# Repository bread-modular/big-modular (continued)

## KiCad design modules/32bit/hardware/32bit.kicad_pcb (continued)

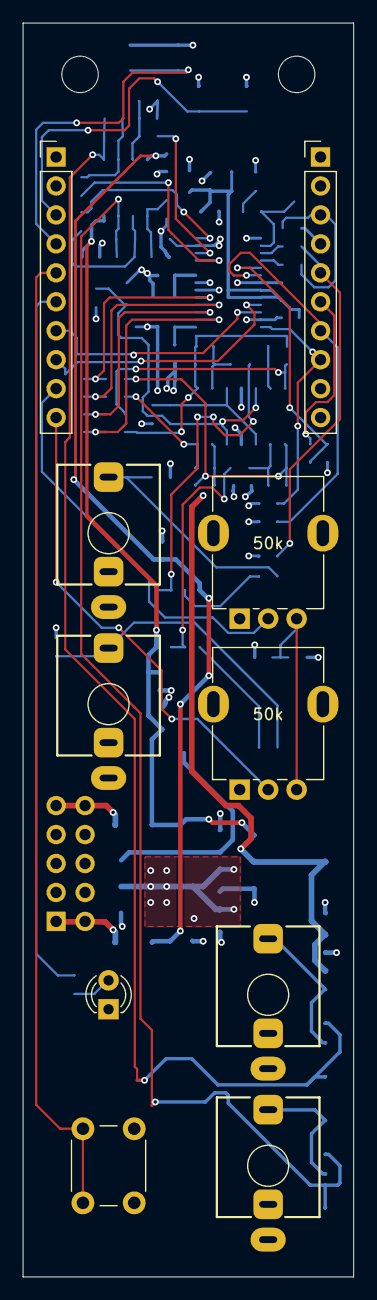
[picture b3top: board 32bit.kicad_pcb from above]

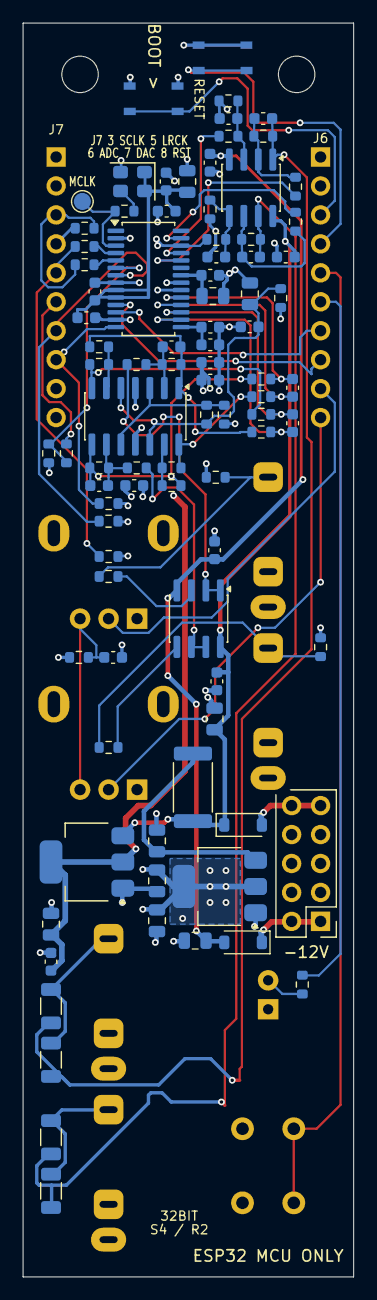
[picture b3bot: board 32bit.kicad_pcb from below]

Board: 4 copper layers, 29.0 x 110.0 mm, 100 parts (90 on the bottom side), 63 nets.

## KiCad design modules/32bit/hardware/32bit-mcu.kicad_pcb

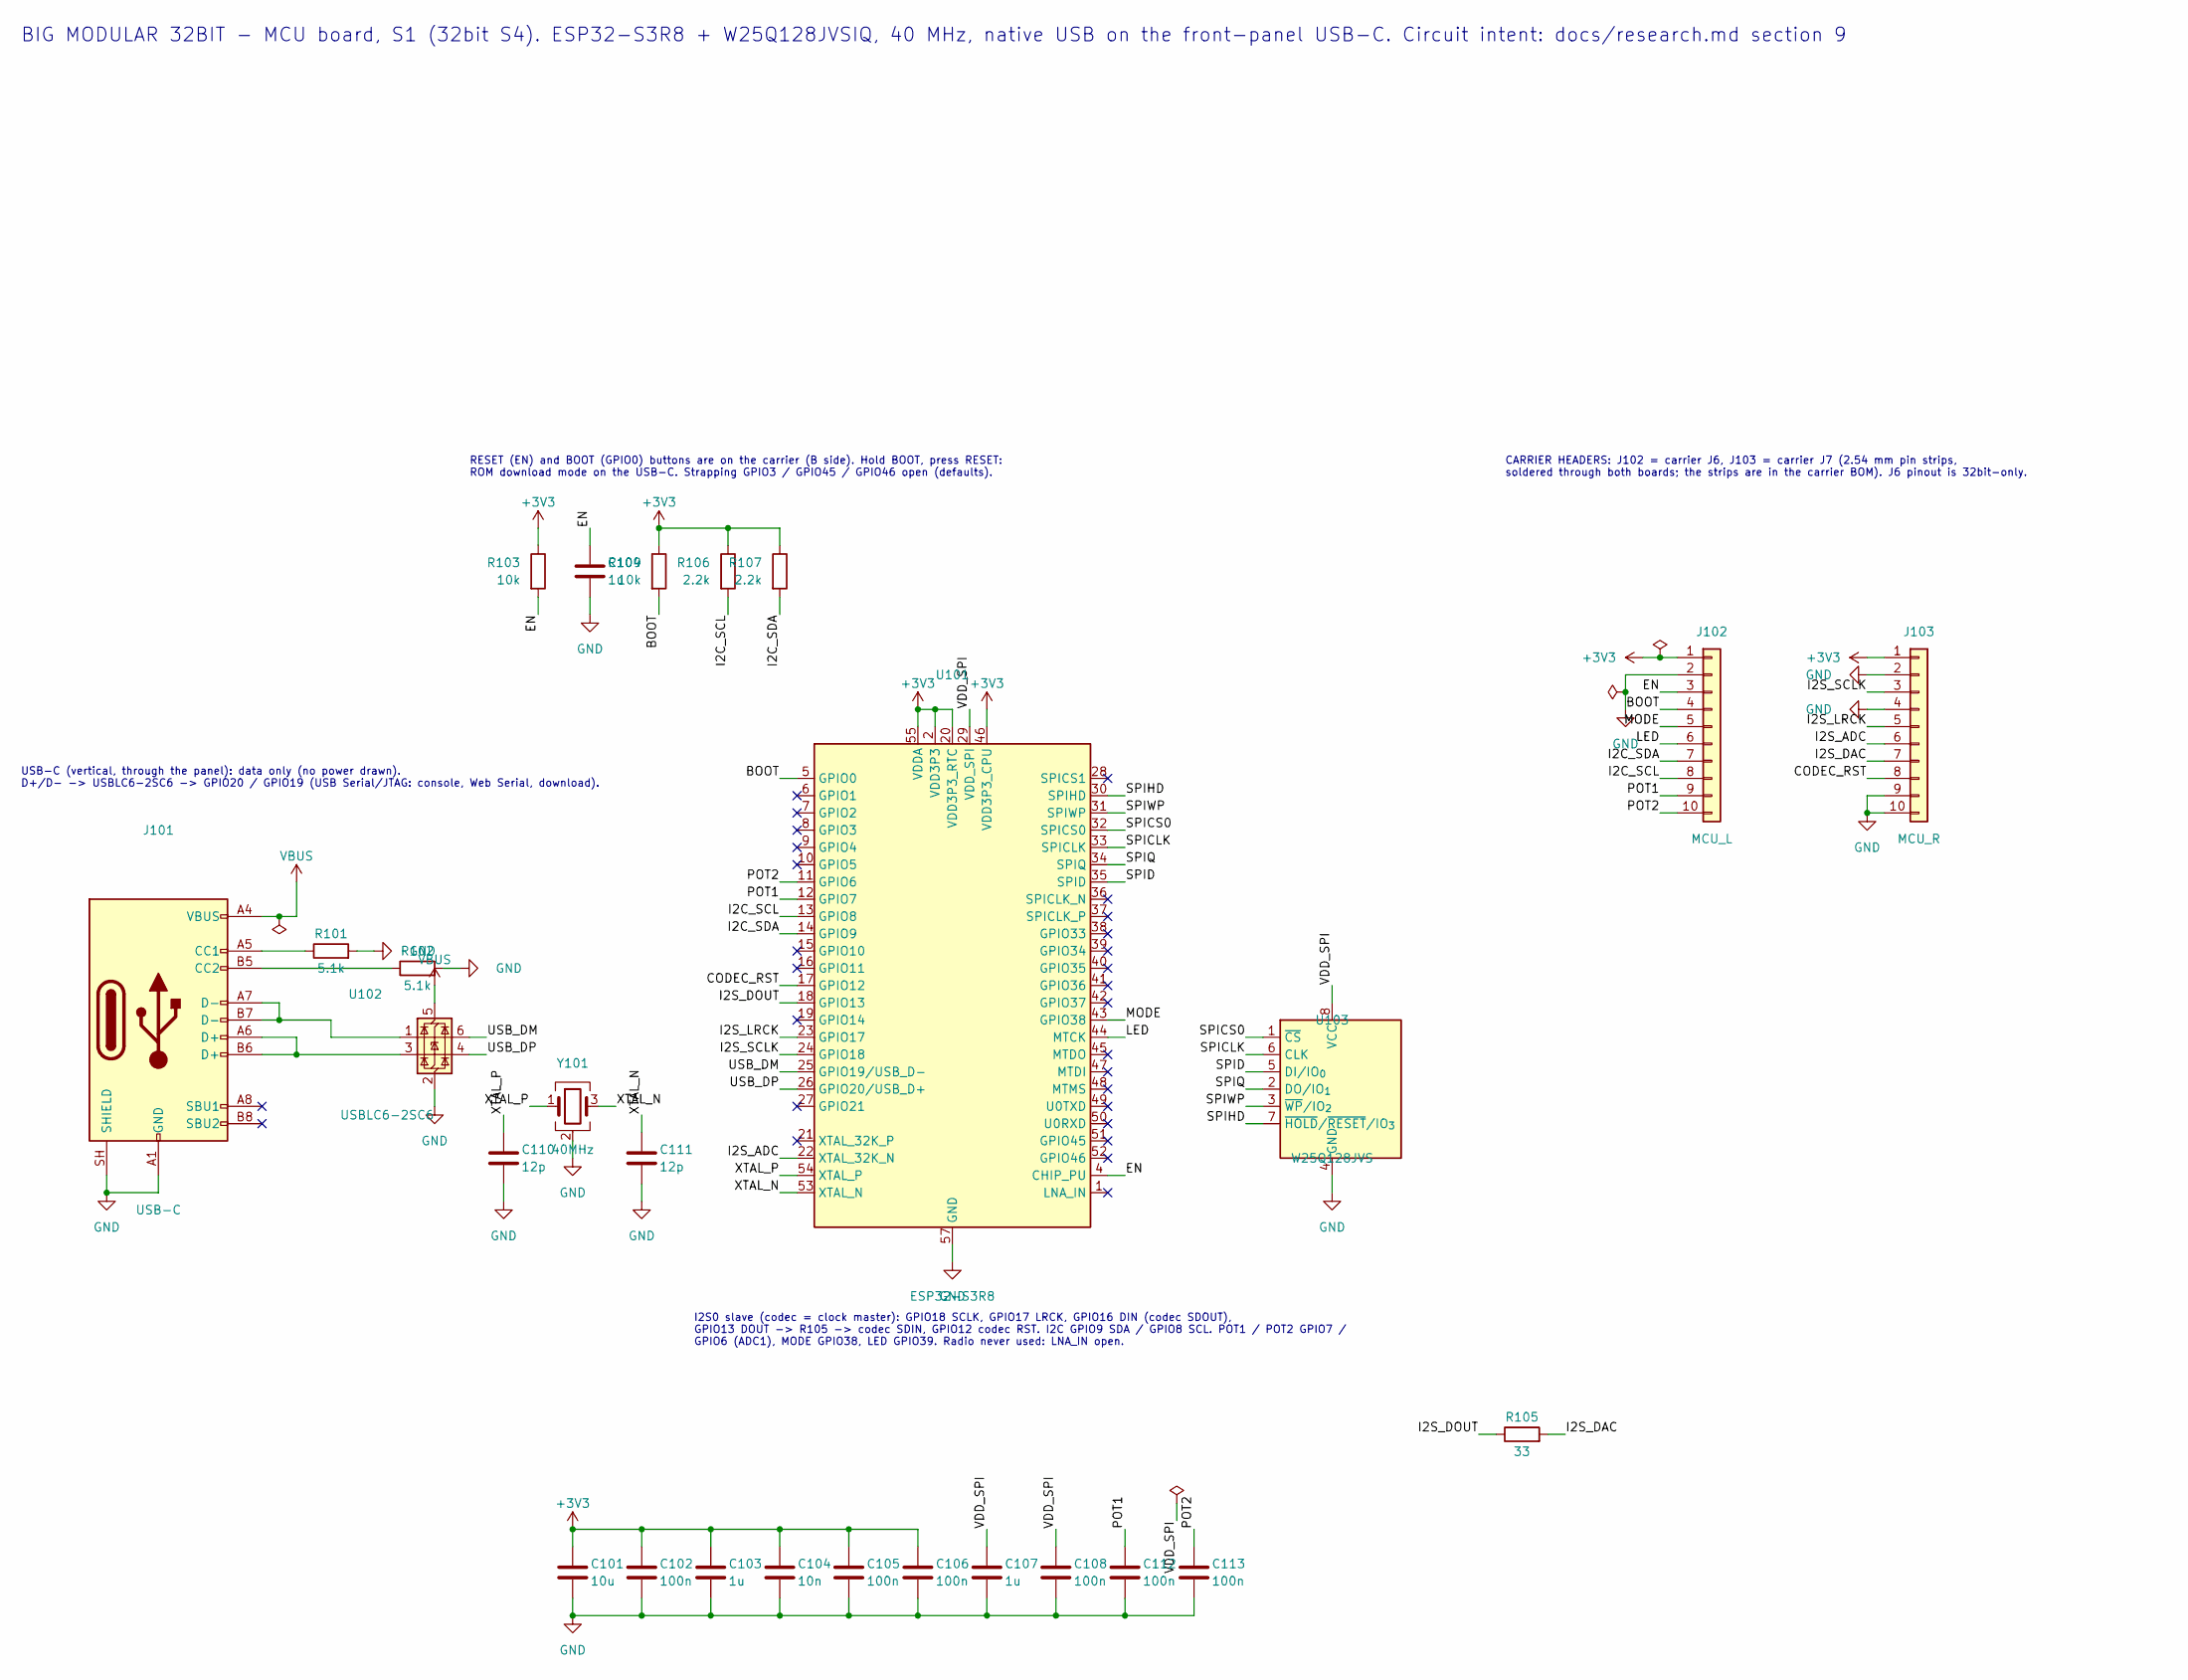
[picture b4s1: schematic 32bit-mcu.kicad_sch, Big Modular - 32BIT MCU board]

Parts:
C101: 10u; C_0603_1608Metric; Voltage 10V; MPN CL10A106KP8NNNC; LCSC C19702
C102, C105, C106, C108, C112, C113: 100n; C_0402_1005Metric; Voltage 16V; MPN CL05B104KO5NNNC; LCSC C1525
C103, C107, C109: 1u; C_0402_1005Metric; Voltage 25V; MPN CL05A105KA5NQNC; LCSC C52923
C104: 10n; C_0402_1005Metric; Voltage 50V; MPN CL05B103KB5NNNC; LCSC C15195
C110, C111: 12p; C_0402_1005Metric; Voltage 50V; MPN 0402CG120J500NT; LCSC C1547
J101: USB-C; USB_C_Receptacle_HRO_TYPE-C-31-D-15_Vertical; MPN TYPE-C-31-D-15; LCSC C22464480
J102: MCU_L; PinHeader_1x10_P2.54mm_Vertical
J103: MCU_R; PinHeader_1x10_P2.54mm_Vertical
R101, R102: 5.1k; R_0402_1005Metric; MPN 0402WGF5101TCE; LCSC C25905
R103, R104: 10k; R_0402_1005Metric; MPN 0402WGF1002TCE; LCSC C25744
R105: 33; R_0402_1005Metric; MPN 0402WGF330JTCE; LCSC C25105
R106, R107: 2.2k; R_0402_1005Metric; MPN 0402WGF2201TCE; LCSC C25879
U101: ESP32-S3R8; QFN-56-1EP_7x7mm_P0.4mm_EP4x4mm_ThermalVias; MPN ESP32-S3R8; LCSC C2913194
U102: USBLC6-2SC6; SOT-23-6; MPN USBLC6-2SC6; LCSC C7519
U103: W25Q128JVS; SOIC-8_5.3x5.3mm_P1.27mm; MPN W25Q128JVSIQ; LCSC C97521
Y101: 40MHz; Crystal_SMD_3225-4Pin_3.2x2.5mm; MPN X322540MMB4SI; LCSC C5210647

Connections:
+3V3: C101.1, C102.1, C103.1, C104.1, C105.1, C106.1, J102.1, J103.1, R103.1, R104.1, R106.1, R107.1, U101.2 (VDD3P3), U101.3 (VDD3P3), U101.20 (VDD3P3_RTC), U101.46 (VDD3P3_CPU), U101.55 (VDDA), U101.56 (VDDA)
/BOOT: J102.4, R104.2, U101.5 (GPIO0)
/CODEC_RST: J103.8, U101.17 (GPIO12)
/EN: C109.1, J102.3, R103.2, U101.4 (CHIP_PU)
/I2C_SCL: J102.8, R106.2, U101.13 (GPIO8)
/I2C_SDA: J102.7, R107.2, U101.14 (GPIO9)
/I2S_ADC: J103.6, U101.22 (XTAL_32K_N)
/I2S_DAC: J103.7, R105.2
/I2S_DOUT: R105.1, U101.18 (GPIO13)
/I2S_LRCK: J103.5, U101.23 (GPIO17)
/I2S_SCLK: J103.3, U101.24 (GPIO18)
/LED: J102.6, U101.44 (MTCK)
/MODE: J102.5, U101.43 (GPIO38)
/POT1: C112.1, J102.9, U101.12 (GPIO7)
/POT2: C113.1, J102.10, U101.11 (GPIO6)
/SPICLK: U101.33 (SPICLK), U103.6 (CLK)
/SPICS0: U101.32 (SPICS0), U103.1 (~CS)
/SPID: U101.35 (SPID), U103.5 (DI/IO_{0})
/SPIHD: U101.30 (SPIHD), U103.7 (~HOLD/~RESET/IO_{3})
/SPIQ: U101.34 (SPIQ), U103.2 (DO/IO_{1})
/SPIWP: U101.31 (SPIWP), U103.3 (~WP/IO_{2})
/USB_DM: U101.25 (GPIO19/USB_D-), U102.6 (I/O1)
/USB_DP: U101.26 (GPIO20/USB_D+), U102.4 (I/O2)
/VDD_SPI: C107.1, C108.1, U101.29 (VDD_SPI), U103.8 (VCC)
/XTAL_N: C111.1, U101.53 (XTAL_N), Y101.3
/XTAL_P: C110.1, U101.54 (XTAL_P), Y101.1
GND: C101.2, C102.2, C103.2, C104.2, C105.2, C106.2, C107.2, C108.2, C109.2, C110.2, C111.2, C112.2, C113.2, J101.A1 (GND), J101.A12 (GND), J101.B1 (GND), J101.B12 (GND), J101.SH (SHIELD), J102.2, J103.2, J103.4, J103.9, J103.10, R101.2, R102.2, U101.57 (GND), U102.2 (GND), U103.4 (GND), Y101.2 (G), Y101.4 (G)
unnamed: J101.A5 (CC1), R101.1
unnamed: J101.B5 (CC2), R102.1
unnamed: J101.A6 (D+), J101.B6 (D+), U102.3 (I/O2)
unnamed: J101.A7 (D-), J101.B7 (D-), U102.1 (I/O1)
VBUS: J101.A4 (VBUS), J101.A9 (VBUS), J101.B4 (VBUS), J101.B9 (VBUS), U102.5 (VBUS)

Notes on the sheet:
I2S0 slave (codec = clock master): GPIO18 SCLK, GPIO17 LRCK, GPIO16 DIN (codec SDOUT), GPIO13 DOUT -> R105 -> codec SDIN, GPIO12 codec RST. I2C GPIO9 SDA / GPIO8 SCL. POT1 / POT2 GPIO7 / GPIO6 (ADC1), MODE GPIO38, LED GPIO39. Radio never used: LNA_IN open.
USB-C (vertical, through the panel): data only (no power drawn). D+/D- -> USBLC6-2SC6 -> GPIO20 / GPIO19 (USB Serial/JTAG: console, Web Serial, download).
CARRIER HEADERS: J102 = carrier J6, J103 = carrier J7 (2.54 mm pin strips, soldered through both boards; the strips are in the carrier BOM). J6 pinout is 32bit-only.
BIG MODULAR 32BIT - MCU board, S1 (32bit S4). ESP32-S3R8 + W25Q128JVSIQ, 40 MHz, native USB on the front-panel USB-C. Circuit intent: docs/research.md section 9
RESET (EN) and BOOT (GPIO0) buttons are on the carrier (B side). Hold BOOT, press RESET: ROM download mode on the USB-C. Strapping GPIO3 / GPIO45 / GPIO46 open (defaults).

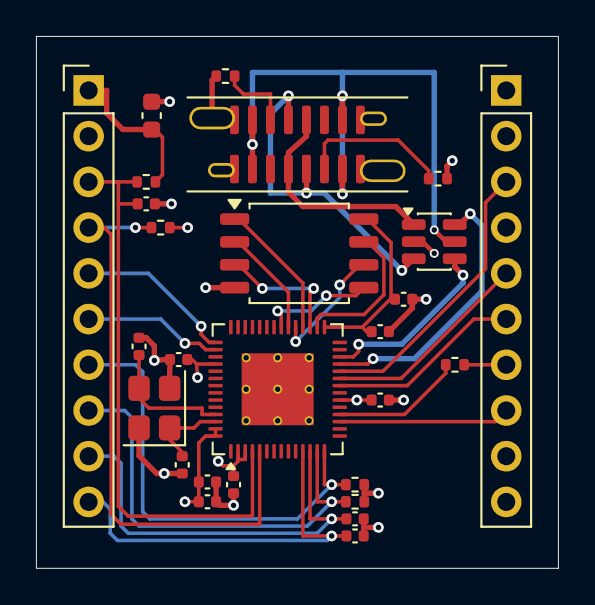
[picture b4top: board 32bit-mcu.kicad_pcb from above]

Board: 4 copper layers, 29.0 x 29.5 mm, 27 parts (0 on the bottom side), 32 nets.
